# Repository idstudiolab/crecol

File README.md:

# Crecol
The fifth team member, a robotic table to alternate between sitting, standing and time-boxed teamwork

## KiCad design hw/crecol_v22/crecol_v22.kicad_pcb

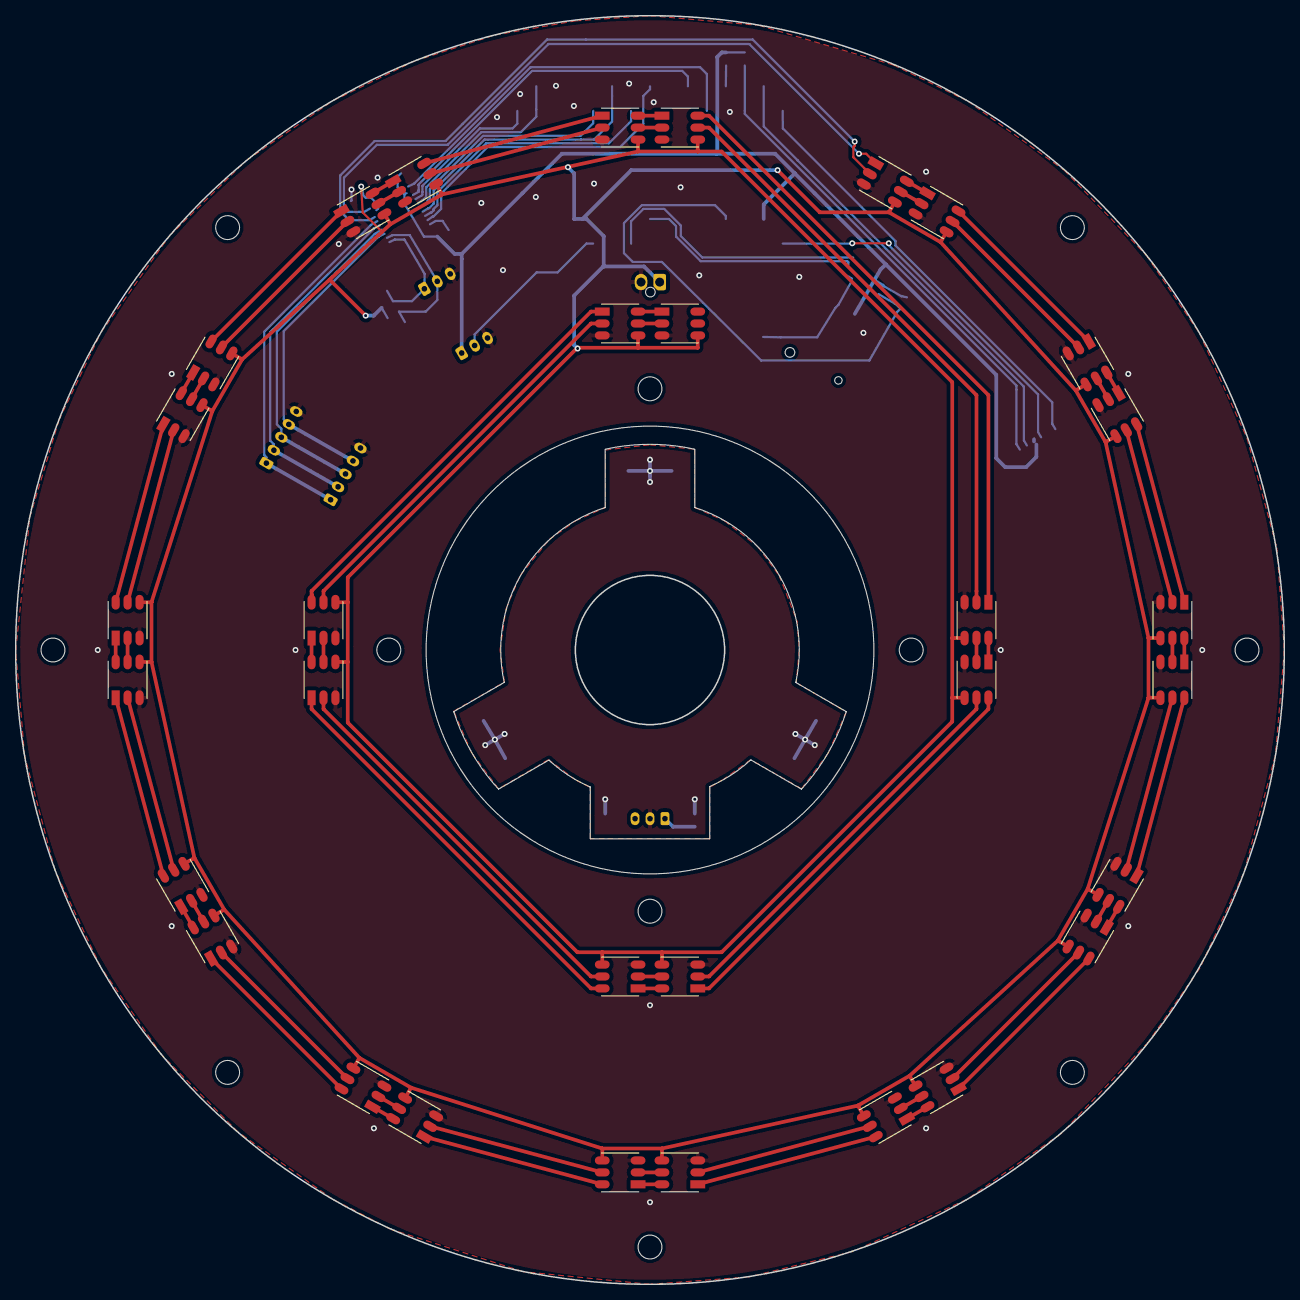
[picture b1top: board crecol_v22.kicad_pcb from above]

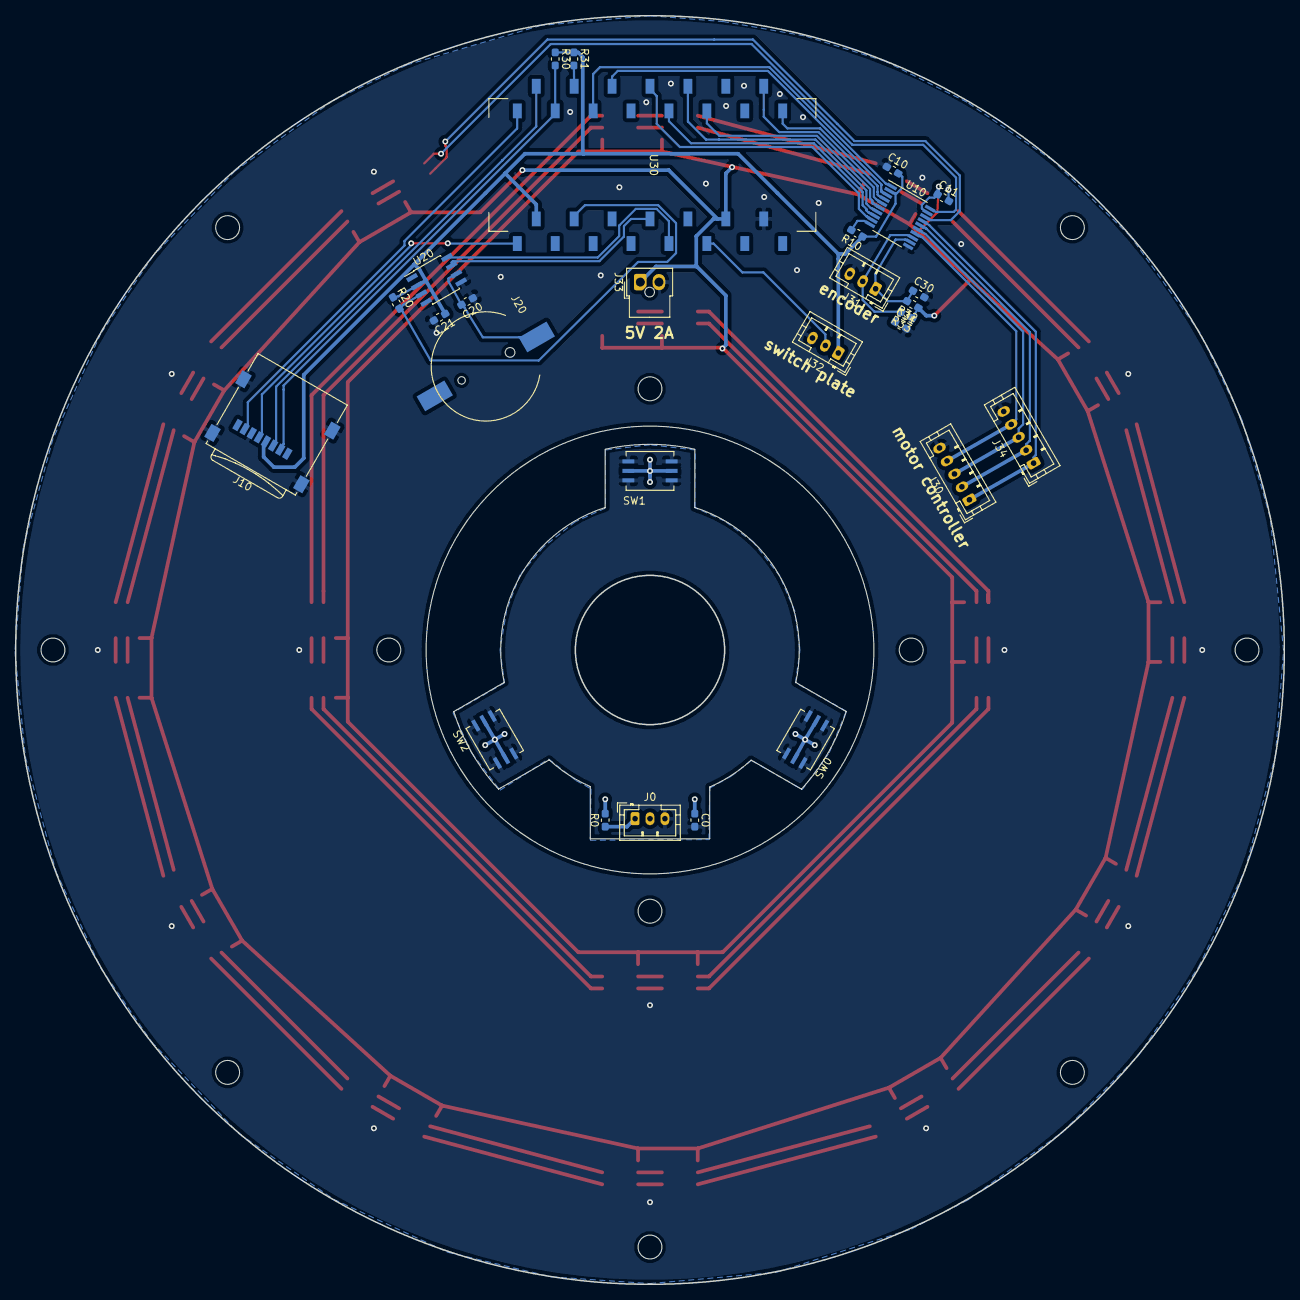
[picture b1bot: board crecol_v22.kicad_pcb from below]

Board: 2 copper layers, 170.0 x 170.0 mm, 60 parts (28 on the bottom side), 93 nets.

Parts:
C0, C10, C11, C20, C21, C30, C31: 100nF; C_0603_1608Metric_Pad1.05x0.95mm_HandSolder
J0: Conn_01x03; JST_PH_B3B-PH-K_1x03_P2.00mm_Vertical
J10: Micro_SD_Card_Det; microSD_HC_Wuerth_693072010801
J20: Batt_clip; CH291-1220LF
J30, J34: JST PH2.0; JST_PH_B5B-PH-K_1x05_P2.00mm_Vertical
J31, J32: JST PH2.0; JST_PH_B3B-PH-K_1x03_P2.00mm_Vertical
J33: Conn_01x02; Molex_Nano-Fit_105309-xx02_1x02_P2.50mm_Vertical
R0, R10, R20, R30, R31, R32, R33: 10K; R_0603_1608Metric_Pad1.05x0.95mm_HandSolder
SW0, SW1, SW2: SPST; RAFI_MICON5_SMD
U1A1, U1B1, U2A1, U2B1, U3A1, U3B1, U4A1, U4B1, U5A1, U5B1, U6A1, U6B1, U7A1, U7B1, U8A1, U8B1, U9A1, U9B1, U10A1, U10B1, U11A1, U11B1, U12A1, U12B1, U13A1, U13B1, U14A1, U14B1, U15A1, U15B1, U16A1, U16B1: APA102; 5050
U10: TXB0108PWR; TSSOP-20_4.4x6.5mm_P0.65mm
U20: DS3231MZ; SOIC-8_3.9x4.9mm_P1.27mm
U30: ARDUINO_NANO_33_IOT; ARDUINO_NANO_33_IOT_SMD_SOCKET_NH

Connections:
+3V3: C10.2, C21.1, J0.1, J10.4, J32.1, R0.1, R10.1, R20.1, R30.1, R31.1, U10.2, U20.2, U30.2
+5V: C11.1, J33.1, R32.1, R33.1, U1A1.4, U1B1.4, U2A1.4, U2B1.4, U3A1.4, U3B1.4, U4A1.4, U4B1.4, U5A1.4, U5B1.4, U6A1.4, U6B1.4, U7A1.4, U7B1.4, U8A1.4, U8B1.4, U9A1.4, U9B1.4, U10.19, U10A1.4, U10B1.4, U11A1.4, U11B1.4, U12A1.4, U12B1.4, U13A1.4, U13B1.4, U14A1.4, U14B1.4, U15A1.4, U15B1.4, U16A1.4, U16B1.4, U30.12
GND: C0.2, C10.1, C11.2, C20.1, C21.2, C30.2, C31.2, J0.3, J10.6, J10.9, J30.5, J31.3, J32.3, J33.2, J34.5, SW0.2, SW1.2, SW2.2, U1A1.3, U1B1.3, U2A1.3, U2B1.3, U3A1.3, U3B1.3, U4A1.3, U4B1.3, U5A1.3, U5B1.3, U6A1.3, U6B1.3, U7A1.3, U7B1.3, U8A1.3, U8B1.3, U9A1.3, U9B1.3, U10.11, U10A1.3, U10B1.3, U11A1.3, U11B1.3, U12A1.3, U12B1.3, U13A1.3, U13B1.3, U14A1.3, U14B1.3, U15A1.3, U15B1.3, U16A1.3, U16B1.3, U20.5, U30.14
K_A_3V: U10.9, U30.23
K_A_5V: C30.1, J31.1, R32.2, U10.12
K_B_3V: U10.8, U30.22
K_B_5V: C31.1, J31.2, R33.2, U10.13
L_CLK_3V: U10.3, U30.25
L_CLK_5V: U1A1.2, U10.18
L_DO_3V: U10.1, U30.26
L_DO_5V: U1A1.1, U10.20
MISO: J10.7, U30.30
MOSI: J10.3, U30.29
unnamed: C0.1, J0.2, R0.2, SW0.1, SW1.1, SW2.1
unnamed: C20.2, J20.1, U20.6
unnamed: R10.2, U10.10
unnamed: U1A1.5, U1B1.2
unnamed: U1A1.6, U1B1.1
unnamed: U1B1.5, U2A1.2
unnamed: U1B1.6, U2A1.1
unnamed: U2A1.5, U2B1.2
unnamed: U2A1.6, U2B1.1
unnamed: U2B1.5, U3A1.2
unnamed: U2B1.6, U3A1.1
unnamed: U3A1.5, U3B1.2
unnamed: U3A1.6, U3B1.1
unnamed: U3B1.5, U4A1.2
unnamed: U3B1.6, U4A1.1
unnamed: U4A1.5, U4B1.2
unnamed: U4A1.6, U4B1.1
unnamed: U4B1.5, U5A1.2
unnamed: U4B1.6, U5A1.1
unnamed: U5A1.5, U5B1.2
unnamed: U5A1.6, U5B1.1
unnamed: U5B1.5, U6A1.2
unnamed: U5B1.6, U6A1.1
unnamed: U6A1.5, U6B1.2
unnamed: U6A1.6, U6B1.1
unnamed: U6B1.5, U7A1.2
unnamed: U6B1.6, U7A1.1
unnamed: U7A1.5, U7B1.2
unnamed: U7A1.6, U7B1.1
unnamed: U7B1.5, U8A1.2
unnamed: U7B1.6, U8A1.1
unnamed: U8A1.5, U8B1.2
unnamed: U8A1.6, U8B1.1
unnamed: U8B1.5, U9A1.2
unnamed: U8B1.6, U9A1.1
unnamed: U9A1.5, U9B1.2
unnamed: U9A1.6, U9B1.1
unnamed: U9B1.6, U10A1.1
unnamed: U9B1.5, U10A1.2
unnamed: U10A1.5, U10B1.2
unnamed: U10A1.6, U10B1.1
unnamed: U10B1.5, U11A1.2
unnamed: U10B1.6, U11A1.1
unnamed: U11A1.5, U11B1.2
unnamed: U11A1.6, U11B1.1
unnamed: U11B1.5, U12A1.2
unnamed: U11B1.6, U12A1.1
unnamed: U12A1.5, U12B1.2
unnamed: U12A1.6, U12B1.1
unnamed: U12B1.5, U13A1.2
unnamed: U12B1.6, U13A1.1
unnamed: U13A1.5, U13B1.2
unnamed: U13A1.6, U13B1.1
unnamed: U13B1.5, U14A1.2
unnamed: U13B1.6, U14A1.1
unnamed: U14A1.5, U14B1.2
unnamed: U14A1.6, U14B1.1
unnamed: U14B1.5, U15A1.2
unnamed: U14B1.6, U15A1.1
unnamed: U15A1.5, U15B1.2
unnamed: U15A1.6, U15B1.1
unnamed: U15B1.5, U16A1.2
unnamed: U15B1.6, U16A1.1
unnamed: U16A1.5, U16B1.2
unnamed: U16A1.6, U16B1.1
RTC_INT: R20.2, U20.3, U30.4
SCK: J10.5, U30.1
SCL: U20.8, U30.9
SDA: U20.7, U30.8
SD_CD: R31.2, U30.27
SD_CS: J10.2, R30.2, U30.28
SW_OUT: J32.2, U30.11
T_HS1(UP)_3V: U10.6, U30.20
T_HS1(UP)_5V: J30.3, J34.3, U10.15
T_HS2(DN)_3V: U10.7, U30.21
T_HS2(DN)_5V: J30.4, J34.4, U10.14
T_RXD_3V: U10.4, U30.16
T_RXD_5V: J30.1, J34.1, U10.17
T_TXD_3V: U10.5, U30.17
T_TXD_5V: J30.2, J34.2, U10.16

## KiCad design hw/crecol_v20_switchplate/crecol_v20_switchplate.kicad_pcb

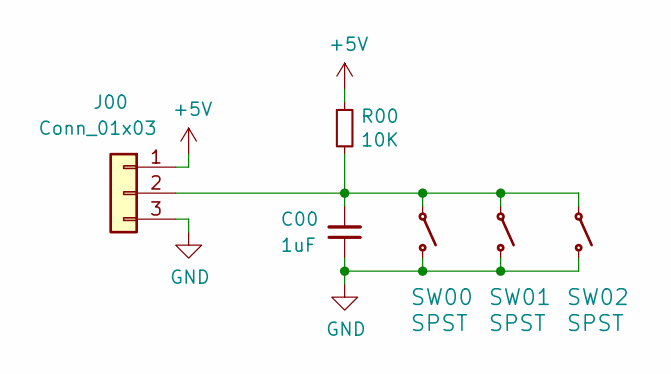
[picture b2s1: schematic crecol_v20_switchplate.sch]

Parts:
C00: 1uF; C_0603_1608Metric
J00: Conn_01x03; JST_PH_B3B-PH-K_1x03_P2.00mm_Vertical
R00: 10K; R_0603_1608Metric
SW00, SW01, SW02: SPST; RAFI_MICON5_SMD

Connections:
+5V: J00.1, R00.1
GND: C00.1, J00.3, SW00.2 (B0), SW01.2 (B0), SW02.2 (B0)
unnamed: C00.2, J00.2, R00.2, SW00.1 (A0), SW01.1 (A0), SW02.1 (A0)

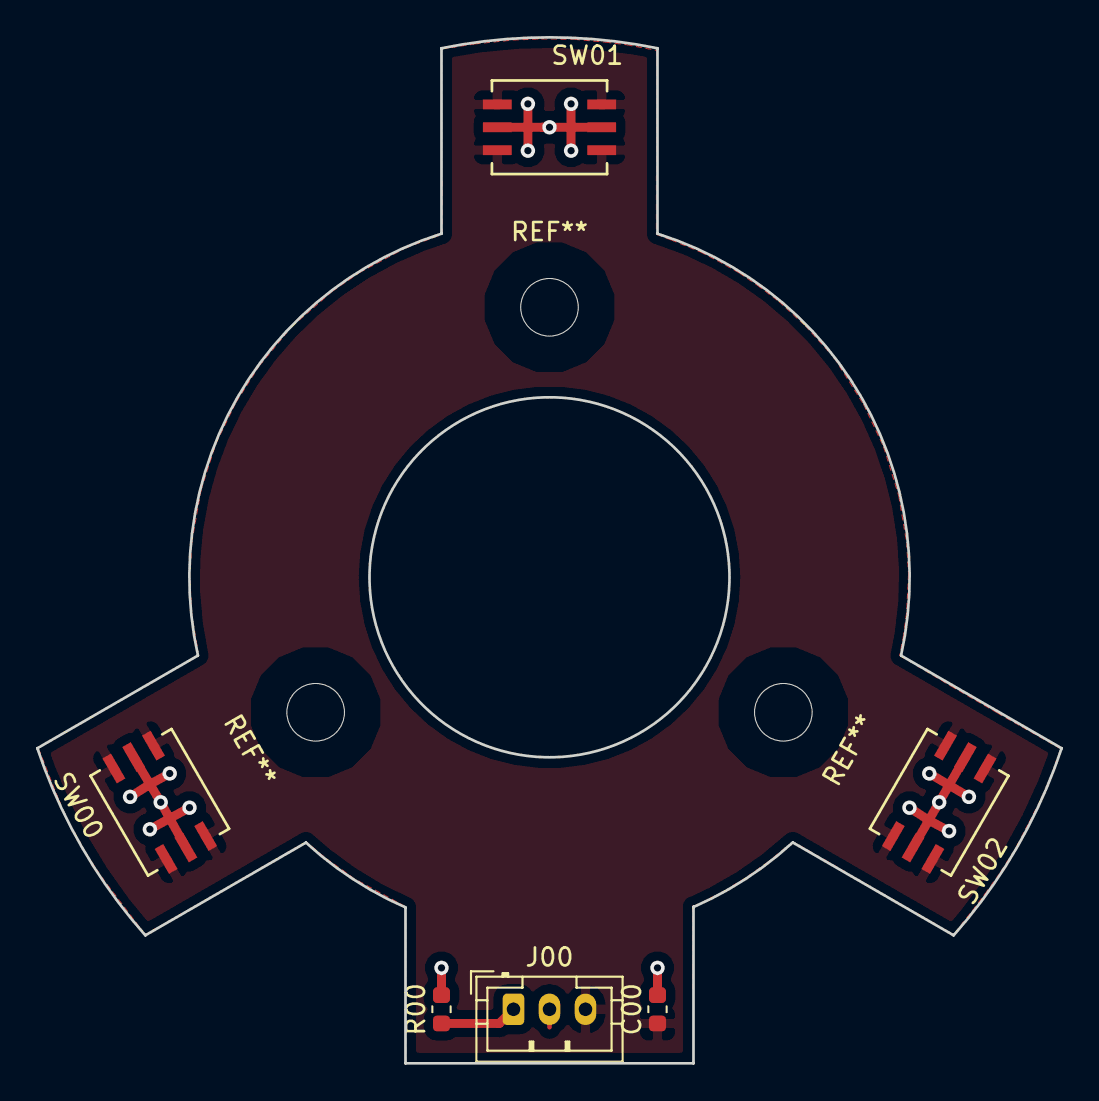
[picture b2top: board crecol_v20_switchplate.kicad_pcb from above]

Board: 2 copper layers, 56.9 x 57.0 mm, 6 parts (0 on the bottom side), 3 nets.

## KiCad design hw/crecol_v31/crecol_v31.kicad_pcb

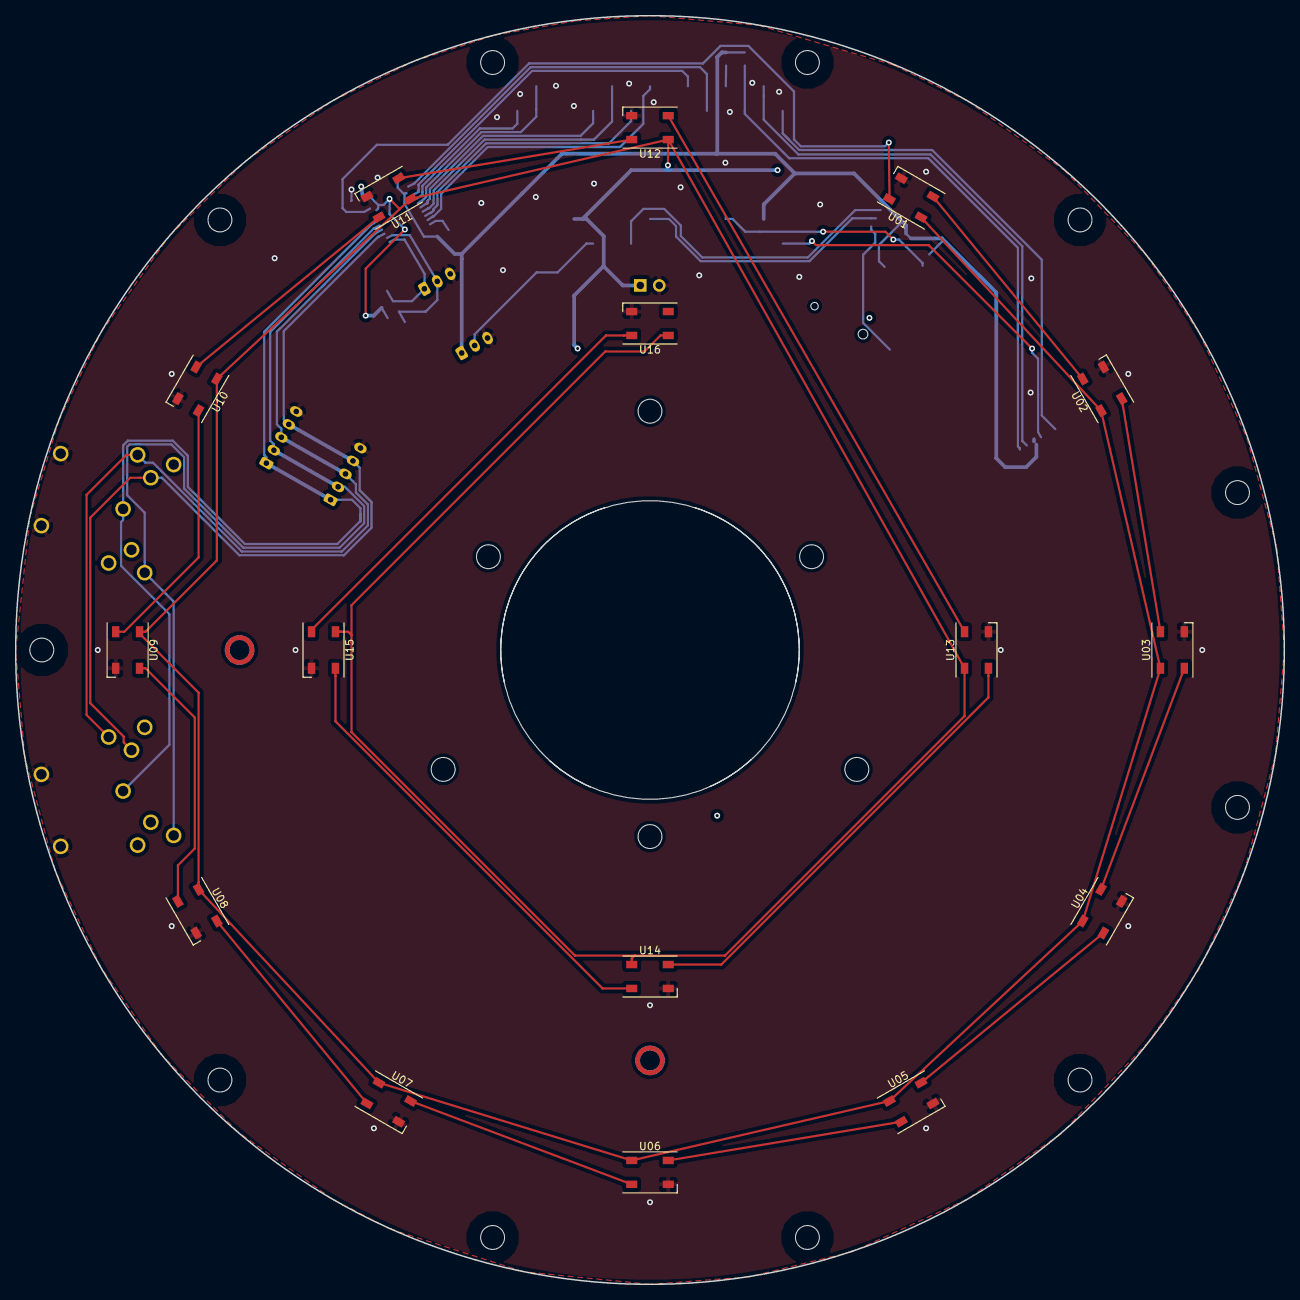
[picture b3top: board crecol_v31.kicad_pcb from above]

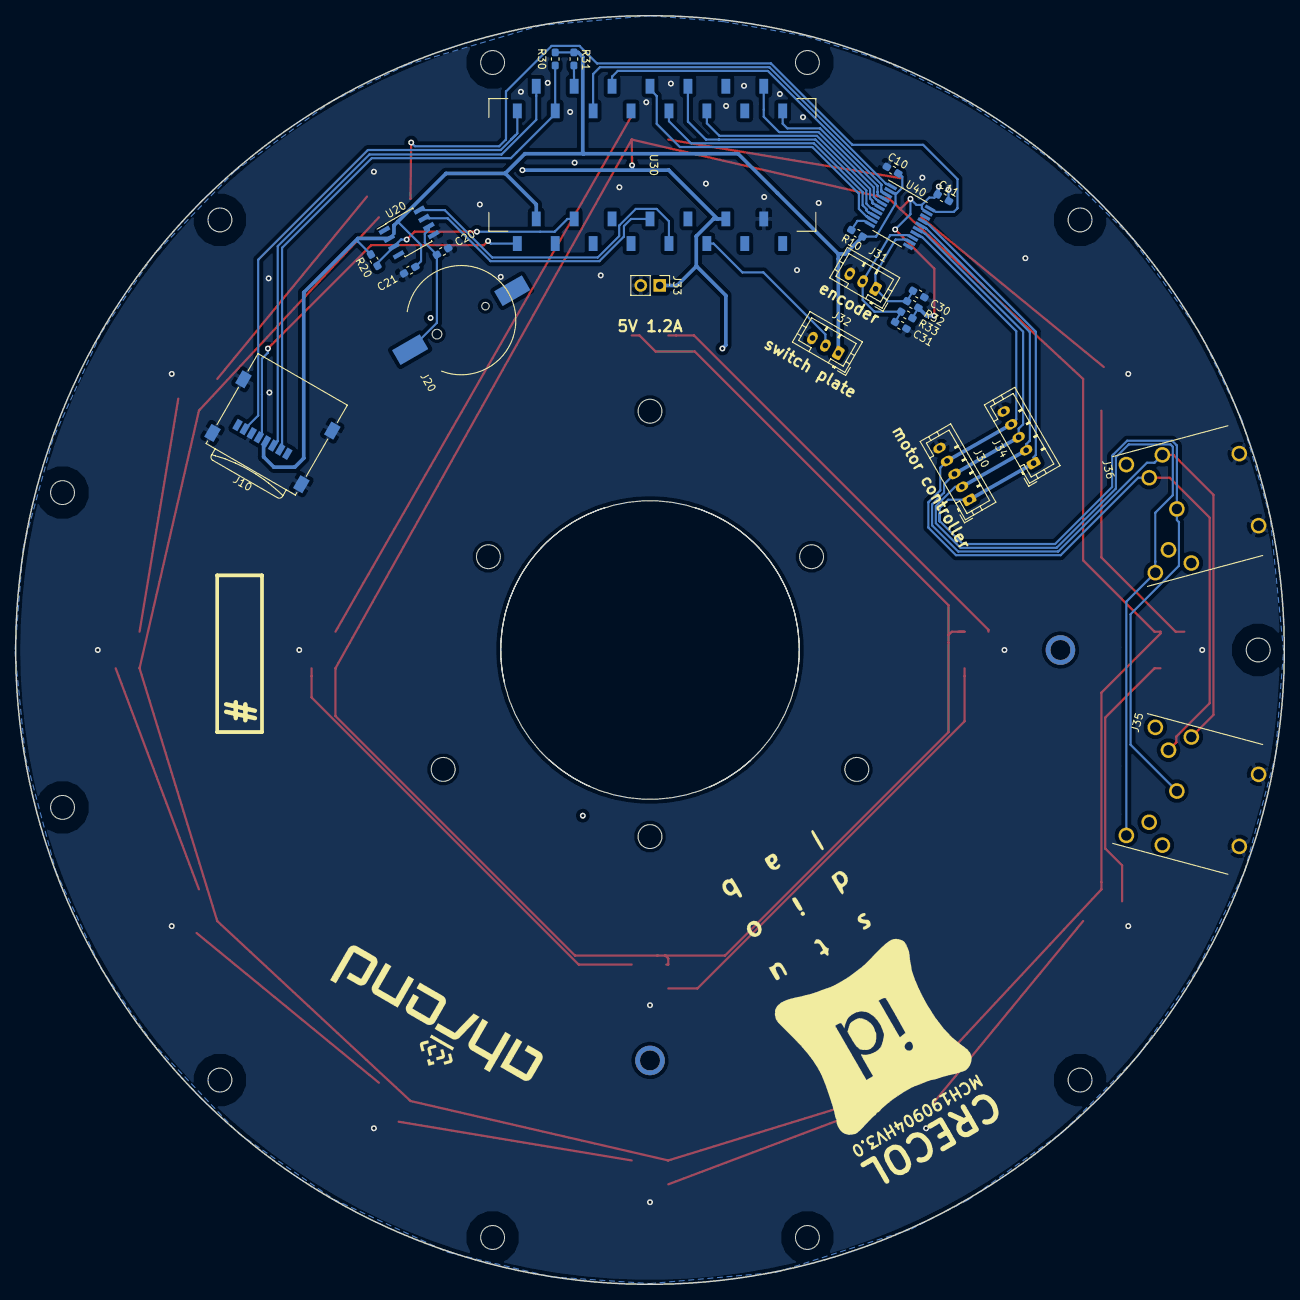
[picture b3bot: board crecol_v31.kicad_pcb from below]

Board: 2 copper layers, 170.0 x 170.0 mm, 41 parts (24 on the bottom side), 44 nets.

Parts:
C10, C11, C20, C21, C30, C31: 100nF; C_0603_1608Metric_Pad1.05x0.95mm_HandSolder
J10: Micro_SD_Card_Det; microSD_HC_Wuerth_693072010801
J20: Batt_clip; CH291-1220LF
J30, J34: JST PH2.0; JST_PH_B5B-PH-K_1x05_P2.00mm_Vertical
J31, J32: JST PH2.0; JST_PH_B3B-PH-K_1x03_P2.00mm_Vertical
J33: Conn_01x02; PinHeader_1x02_P2.54mm_Vertical
J35, J36: DIN-7; PSG03465
R10, R20, R30, R31, R32, R33: 10K; R_0603_1608Metric_Pad1.05x0.95mm_HandSolder
U01, U02, U03, U04, U05, U06, U07, U08, U09, U10, U11, U12, U13, U14, U15, U16: SK6812; LED_SK6812_PLCC4_5.0x5.0mm_P3.2mm
U20: DS3231MZ; SOIC-8_3.9x4.9mm_P1.27mm
U30: ARDUINO_NANO_33_IOT; ARDUINO_NANO_33_IOT_SMD_SOCKET_NH
U40: TXB0108PWR; TSSOP-20_4.4x6.5mm_P0.65mm
e: MountingHole_3.2mm_M3

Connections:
+3V3: C10.2, C21.1, J10.4, J32.1, R10.1, R20.1, R30.1, R31.1, U20.2, U30.2, U40.2
+5V: C11.1, J33.1, R32.1, R33.1, U01.3, U02.3, U03.3, U04.3, U05.3, U06.3, U07.3, U08.3, U09.3, U10.3, U11.3, U12.3, U13.3, U14.3, U15.3, U16.3, U30.12, U40.19
GND: C10.1, C11.2, C20.1, C21.2, C30.2, C31.2, J10.6, J10.9, J30.5, J31.3, J32.3, J33.2, J34.5, J35.S, J36.S, U01.1, U02.1, U03.1, U04.1, U05.1, U06.1, U07.1, U08.1, U09.1, U10.1, U11.1, U12.1, U13.1, U14.1, U15.1, U16.1, U20.5, U30.14, U40.11
K_A_3V: U30.23, U40.9
K_A_5V: C30.1, J31.1, R32.2, U40.12
K_B_3V: U30.22, U40.8
K_B_5V: C31.1, J31.2, R33.2, U40.13
L_CLK_3V: U30.25, U40.3
L_DO_3V: U30.26, U40.1
L_DO_5V: U01.2, U40.20
MISO: J10.7, U30.30
MOSI: J10.3, U30.29
unnamed: C20.2, J20.1, U20.6
unnamed: R10.2, U40.10
unnamed: U01.4, U02.2
unnamed: U02.4, U03.2
unnamed: U03.4, U04.2
unnamed: U04.4, U05.2
unnamed: U05.4, U06.2
unnamed: U06.4, U07.2
unnamed: U07.4, U08.2
unnamed: U08.4, U09.2
unnamed: U09.4, U10.2
unnamed: U10.4, U11.2
unnamed: U11.4, U12.2
unnamed: U12.4, U13.2
unnamed: U13.4, U14.2
unnamed: U14.4, U15.2
unnamed: U15.4, U16.2
RTC_INT: R20.2, U20.3, U30.4
SCK: J10.5, U30.1
SCL: U20.8, U30.9
SDA: U20.7, U30.8
SD_CD: R31.2, U30.27
SD_CS: J10.2, R30.2, U30.28
SW_OUT: J32.2, U30.11
T_HS1(UP)_3V: U30.20, U40.6
T_HS1(UP)_5V: J30.3, J34.3, J35.3, J36.3, U40.15
T_HS2(DN)_3V: U30.21, U40.7
T_HS2(DN)_5V: J30.4, J34.4, J35.5, J36.5, U40.14
T_RXD_3V: U30.16, U40.4
T_RXD_5V: J30.1, J34.1, J35.1, J36.1, U40.17
T_TXD_3V: U30.17, U40.5
T_TXD_5V: J30.2, J34.2, J35.6, J36.6, U40.16

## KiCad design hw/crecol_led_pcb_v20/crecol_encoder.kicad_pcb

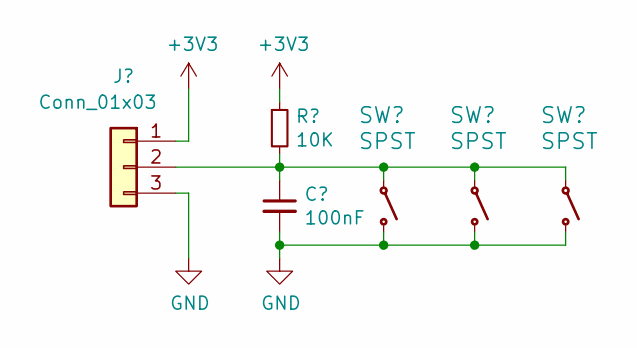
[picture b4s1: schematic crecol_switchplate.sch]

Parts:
C0: 100nF; C_0603_1608Metric_Pad1.05x0.95mm_HandSolder
J0: Conn_01x03; JST_PH_B3B-PH-K_1x03_P2.00mm_Vertical
R0: 10K; R_0603_1608Metric_Pad1.05x0.95mm_HandSolder
SW0, SW1, SW2: SPST; RAFI_MICON5_SMD

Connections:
+3V3: J0.1, R0.1
GND: C0.2, J0.3, SW0.2 (B0), SW1.2 (B0), SW2.2 (B0)
unnamed: C0.1, J0.2, R0.2, SW0.1 (A0), SW1.1 (A0), SW2.1 (A0)

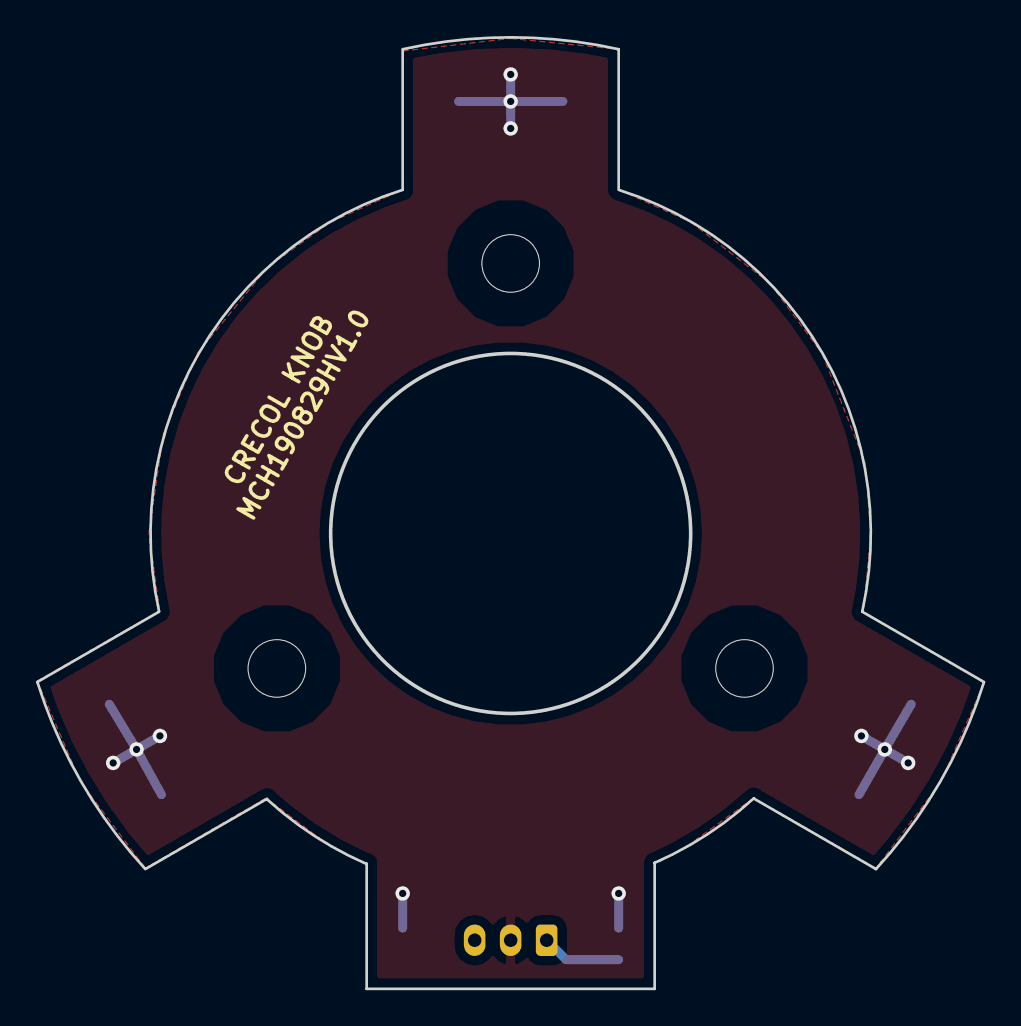
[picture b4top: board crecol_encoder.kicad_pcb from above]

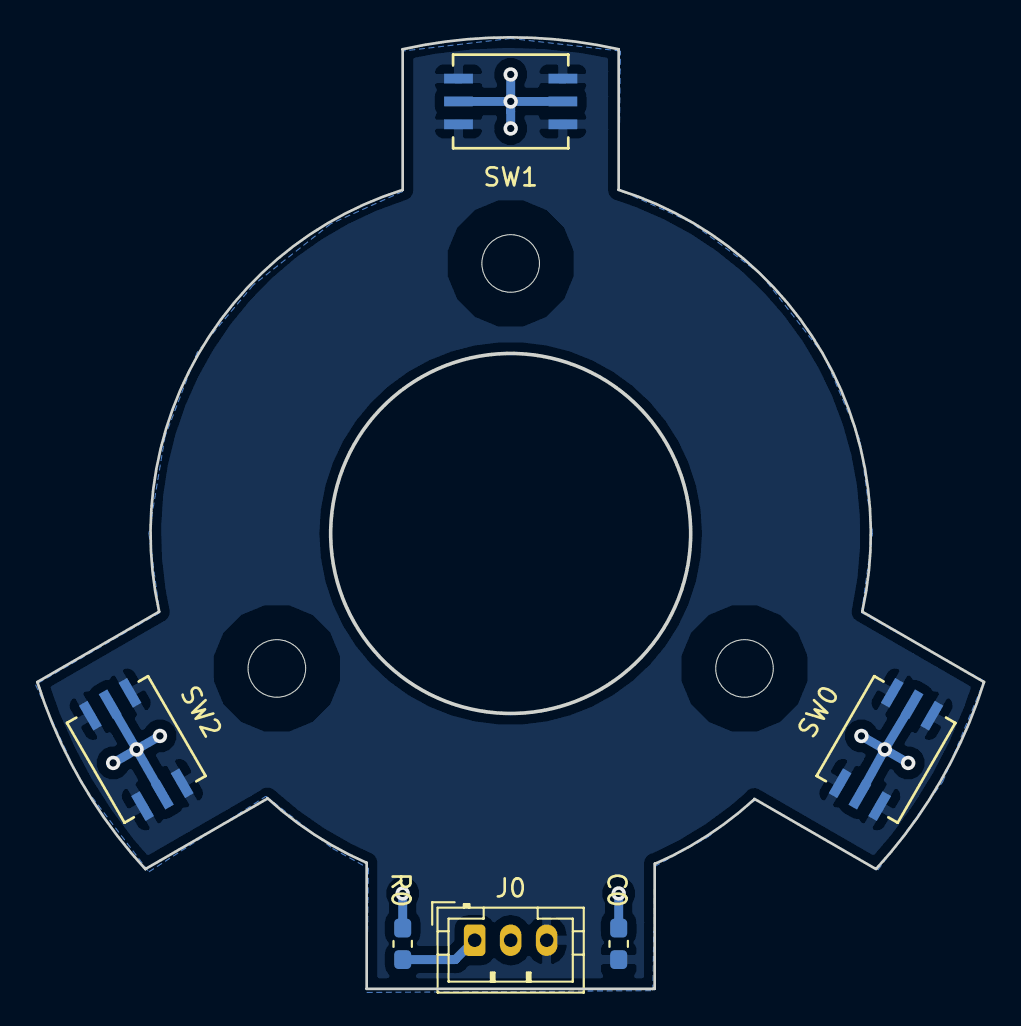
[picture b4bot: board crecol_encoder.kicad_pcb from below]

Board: 2 copper layers, 52.6 x 52.9 mm, 6 parts (6 on the bottom side), 3 nets.

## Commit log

2019-09-20 First post
